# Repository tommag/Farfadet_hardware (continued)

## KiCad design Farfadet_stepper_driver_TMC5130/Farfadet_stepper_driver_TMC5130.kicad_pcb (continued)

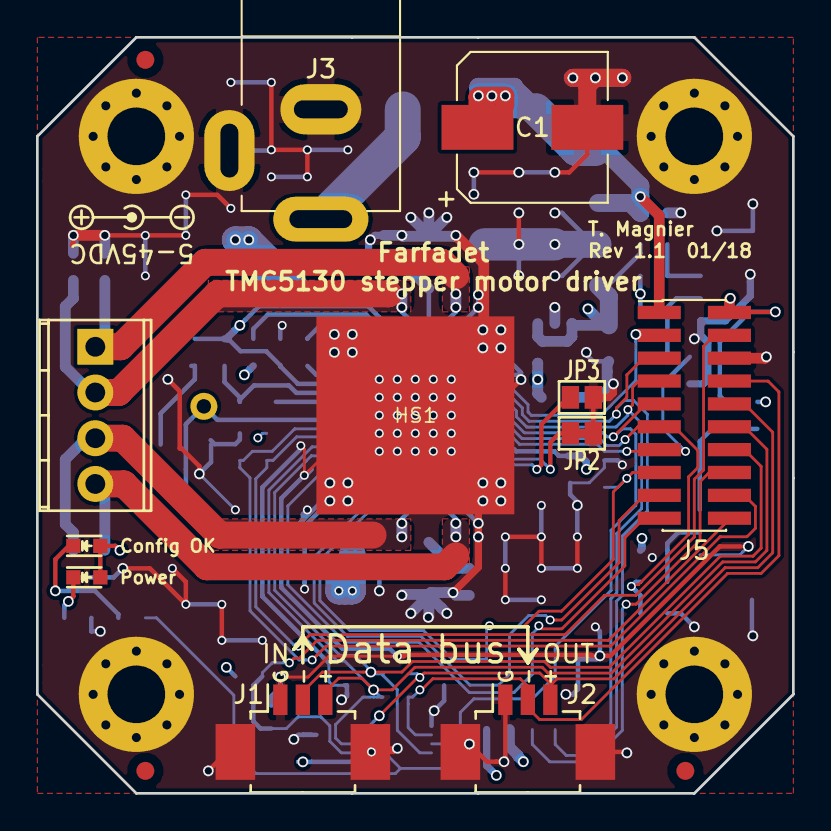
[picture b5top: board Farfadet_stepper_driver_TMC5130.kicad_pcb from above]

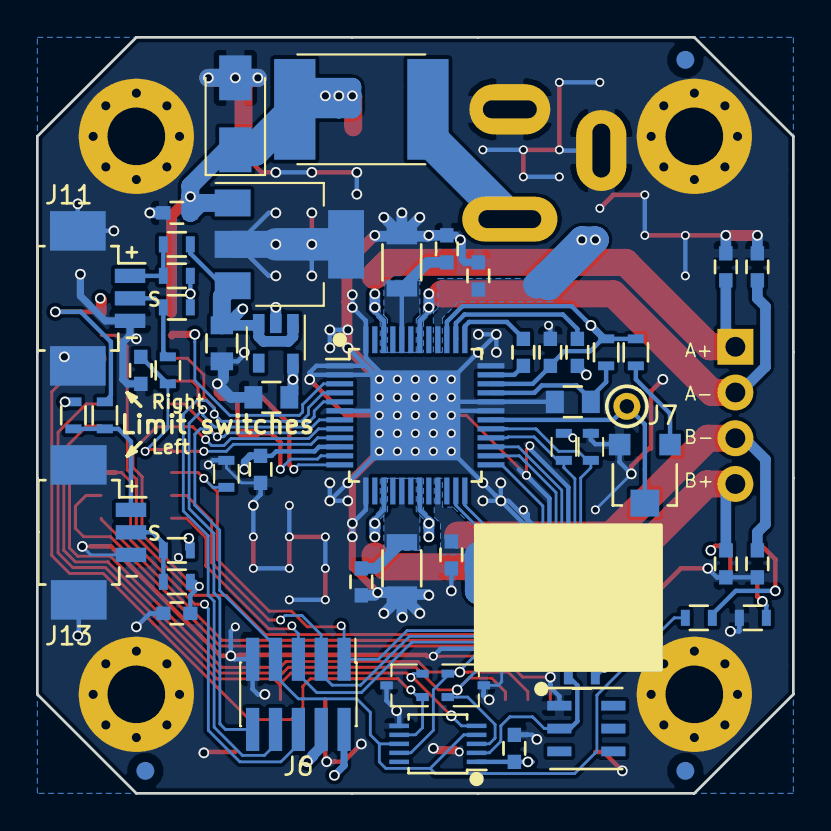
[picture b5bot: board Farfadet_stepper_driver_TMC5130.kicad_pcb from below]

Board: 4 copper layers, 42.0 x 42.0 mm, 72 parts (58 on the bottom side), 42 nets.

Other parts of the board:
FID1, FID2, FID3, FID4, FID5, FID6: Fiducial_very_small_modern

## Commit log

2018-05-18 Add hardware files for the following PCBs : * TMC5130 stepper motor driver v1.1 * Magnetic encoder extension v1.0 * XLR connector extension v1.0 * Minimal 5V / 3.3V differential transceiver v1.0
2018-06-13 Differential transceiver : fix XLR connector pinout
2018-06-13 Magnetic encoder extension v1.1 : add resistive voltage dividers on 5V signals
2018-06-13 Add Farfadet dual transceiver FeatherWing v1.0
2018-06-13 Add Gerber archives
2018-06-13 Add KiCad cache lib files to all designs
2018-06-13 Update Magnetic encoder extension BOM
2018-06-20 Update magnetic encoder extension v1.1 fab drawing
